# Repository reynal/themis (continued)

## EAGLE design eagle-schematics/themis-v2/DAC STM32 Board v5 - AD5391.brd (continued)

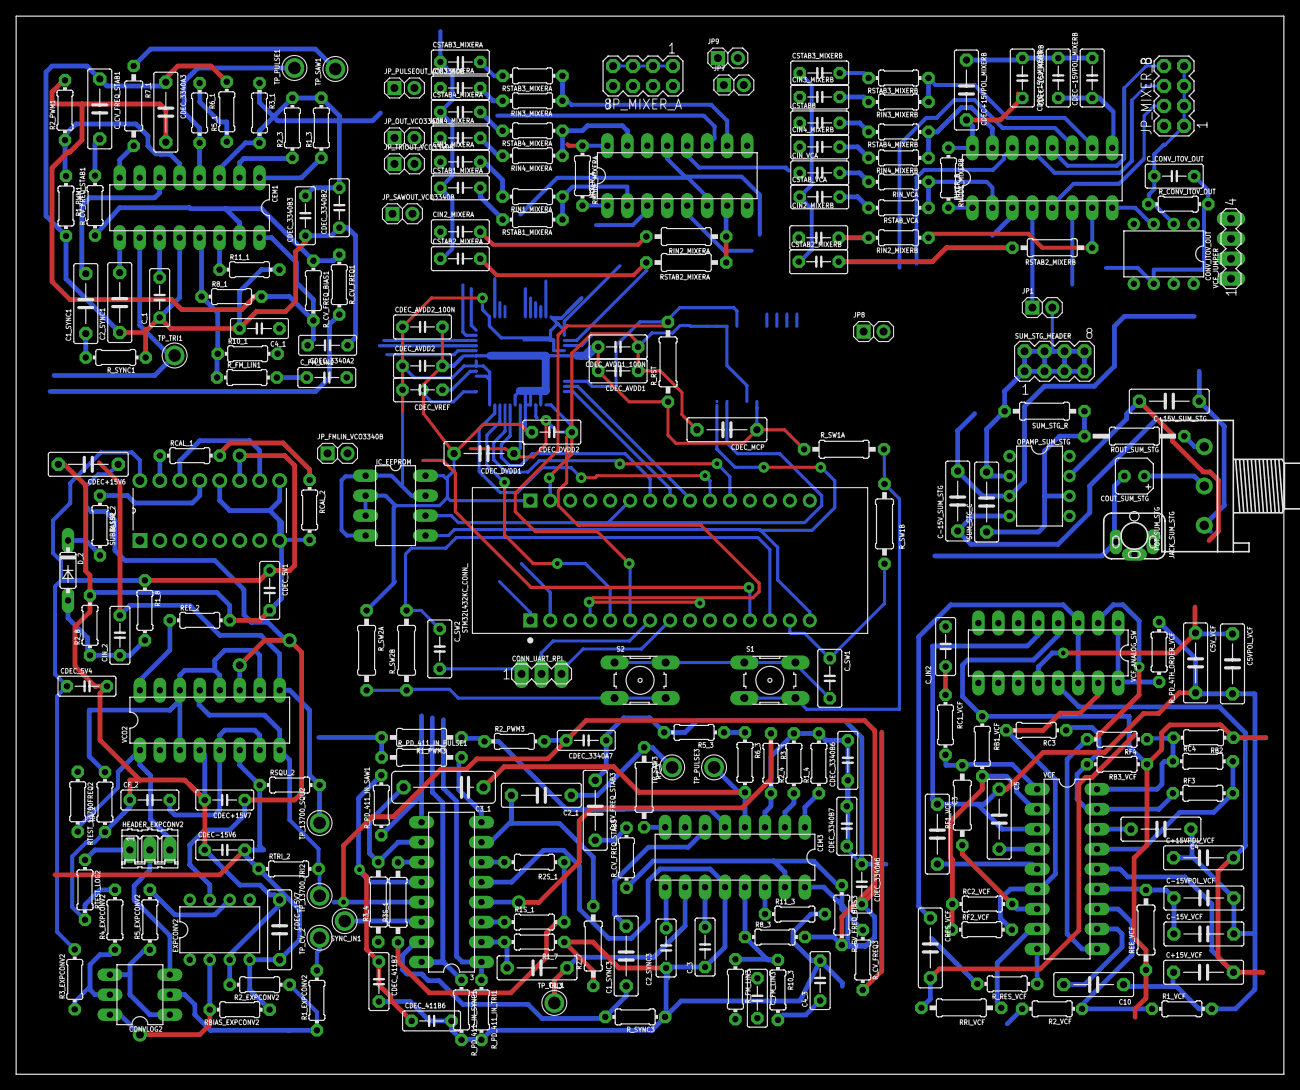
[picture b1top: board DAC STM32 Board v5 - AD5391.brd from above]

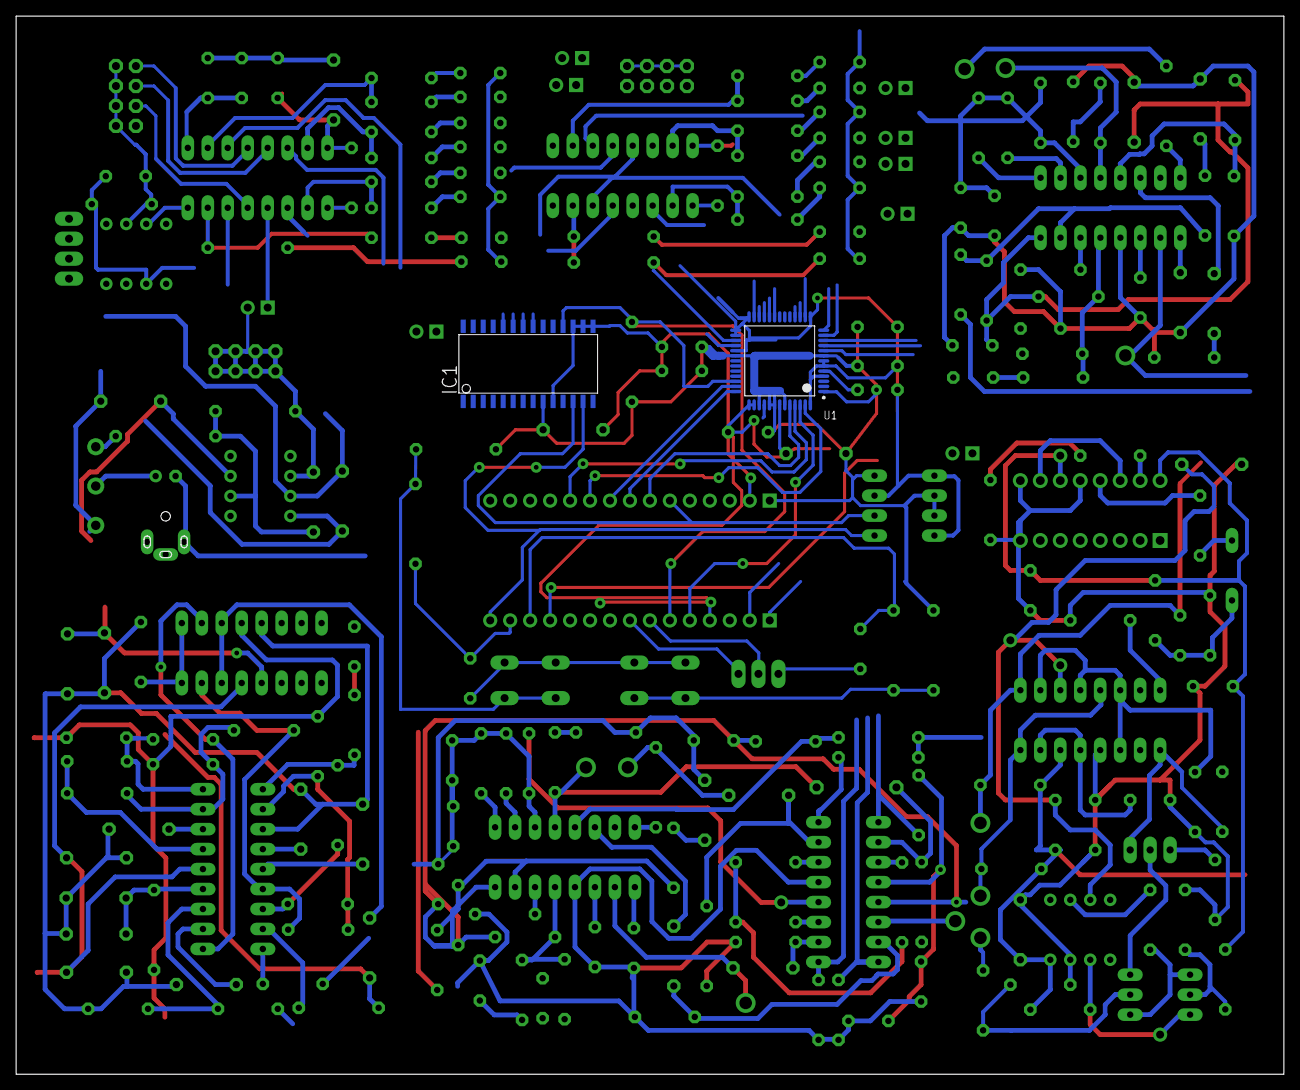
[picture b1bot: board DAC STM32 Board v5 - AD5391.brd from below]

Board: 2 copper layers, 161.3 x 134.6 mm, 229 parts (2 on the bottom side), 173 nets.

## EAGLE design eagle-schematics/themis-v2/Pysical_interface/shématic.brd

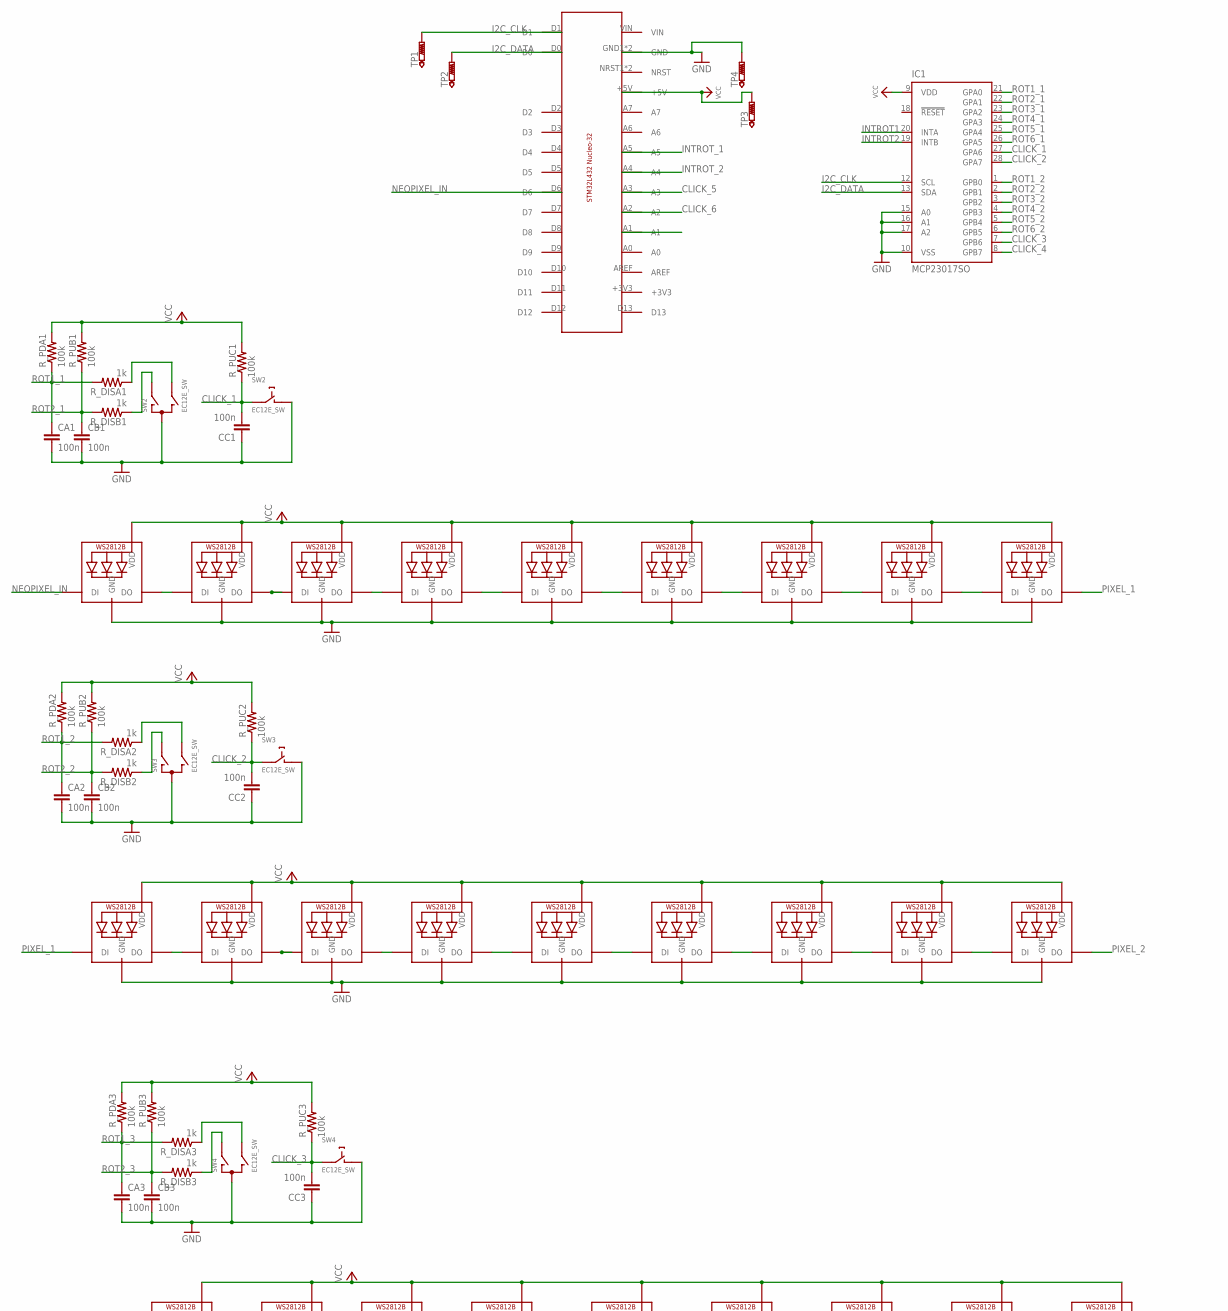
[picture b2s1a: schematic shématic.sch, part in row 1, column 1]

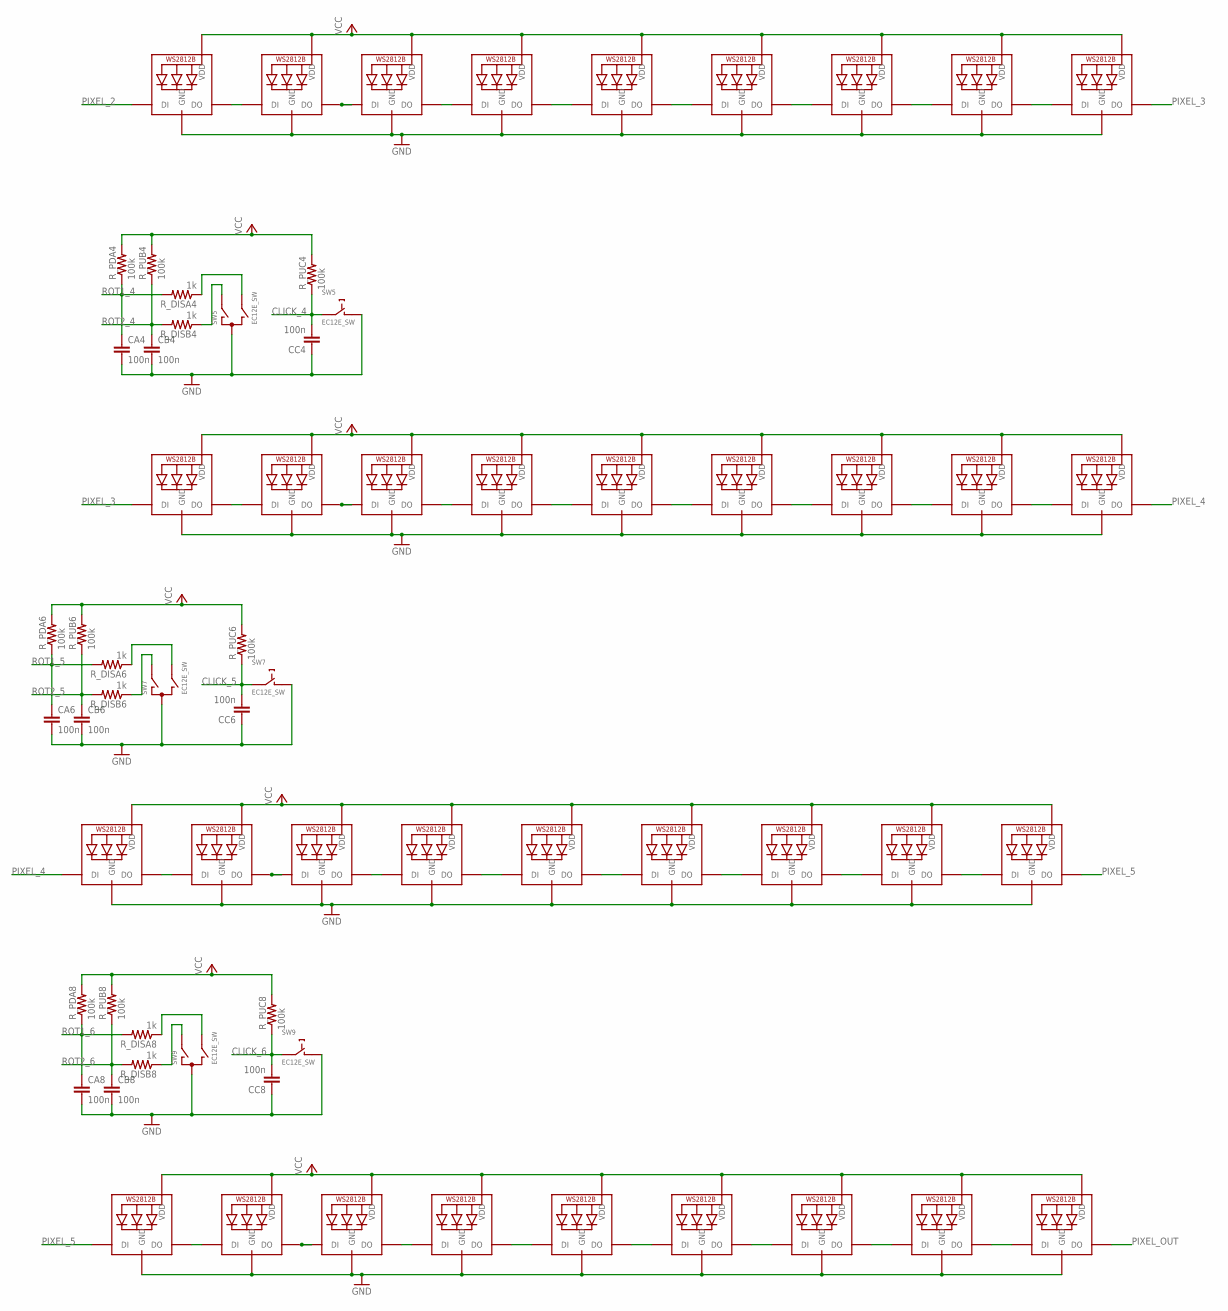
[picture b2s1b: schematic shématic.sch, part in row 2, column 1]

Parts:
CA1, CA2, CA3, CA4, CA6, CA8: 100n; C1210
CB1, CB2, CB3, CB4, CB6, CB8: 100n; C1210
CC1, CC2, CC3, CC4, CC6, CC8: 100n; C1210
IC1: MCP23017SO; SO28W
LED10, LED11, LED12, LED13, LED14, LED15, LED16, LED17, LED18, LED19, LED20, LED21, LED22, LED23, LED24, LED25, LED26, LED27, LED28, LED29, LED30, LED31, LED32, LED33, LED34, LED35, LED36, LED37, LED38, LED39, LED40, LED41, LED42, LED43, LED44, LED45, LED55, LED56, LED57, LED58, LED59, LED60, LED61, LED62, LED63, LED73, LED74, LED75, LED76, LED77, LED78, LED79, LED80, LED81: WS2812B5050; WS2812B
R_DISA1, R_DISA2, R_DISA3, R_DISA4, R_DISA6, R_DISA8: 1k; R1210
R_DISB1, R_DISB2, R_DISB3, R_DISB4, R_DISB6, R_DISB8: 1k; R1210
R_PDA1, R_PDA2, R_PDA3, R_PDA4, R_PDA6, R_PDA8: 100k; R1210
R_PUB1, R_PUB2, R_PUB3, R_PUB4, R_PUB6, R_PUB8: 100k; R1210
R_PUC1, R_PUC2, R_PUC3, R_PUC4, R_PUC6, R_PUC8: 100k; R1210
SW2, SW3, SW4, SW5, SW7, SW9: EC12E_SW; ALPS_EC12E_SW
TP1, TP2, TP3, TP4: PTR1PAD1-13Y; P1-13Y
U$2: NUCLEO-HEADER

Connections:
CLICK_1: CC1.2, IC1.27 (GPA6), R_PUC1.1, SW2.E (2)
CLICK_2: CC2.2, IC1.28 (GPA7), R_PUC2.1, SW3.E (2)
CLICK_3: CC3.2, IC1.7 (GPB6), R_PUC3.1, SW4.E (2)
CLICK_4: CC4.2, IC1.8 (GPB7), R_PUC4.1, SW5.E (2)
CLICK_5: CC6.2, R_PUC6.1, SW7.E (2), U$2.A3
CLICK_6: CC8.2, R_PUC8.1, SW9.E (2), U$2.A2
GND: CA1.2, CA2.2, CA3.2, CA4.2, CA6.2, CA8.2, CB1.2, CB2.2, CB3.2, CB4.2, CB6.2, CB8.2, CC1.1, CC2.1, CC3.1, CC4.1, CC6.1, CC8.1, IC1.10 (VSS), IC1.15 (A0), IC1.16 (A1), IC1.17 (A2), LED10.3-GND (GND), LED11.3-GND (GND), LED12.3-GND (GND), LED13.3-GND (GND), LED14.3-GND (GND), LED15.3-GND (GND), LED16.3-GND (GND), LED17.3-GND (GND), LED18.3-GND (GND), LED19.3-GND (GND), LED20.3-GND (GND), LED21.3-GND (GND), LED22.3-GND (GND), LED23.3-GND (GND), LED24.3-GND (GND), LED25.3-GND (GND), LED26.3-GND (GND), LED27.3-GND (GND), LED28.3-GND (GND), LED29.3-GND (GND), LED30.3-GND (GND), LED31.3-GND (GND), LED32.3-GND (GND), LED33.3-GND (GND), LED34.3-GND (GND), LED35.3-GND (GND), LED36.3-GND (GND), LED37.3-GND (GND), LED38.3-GND (GND), LED39.3-GND (GND), LED40.3-GND (GND), LED41.3-GND (GND), LED42.3-GND (GND), LED43.3-GND (GND), LED44.3-GND (GND), LED45.3-GND (GND), LED55.3-GND (GND), LED56.3-GND (GND), LED57.3-GND (GND), LED58.3-GND (GND), LED59.3-GND (GND), LED60.3-GND (GND), LED61.3-GND (GND), LED62.3-GND (GND), LED63.3-GND (GND), LED73.3-GND (GND), LED74.3-GND (GND), LED75.3-GND (GND), LED76.3-GND (GND), LED77.3-GND (GND), LED78.3-GND (GND), LED79.3-GND (GND), LED80.3-GND (GND), LED81.3-GND (GND), SW2.C, SW2.D (1), SW3.C, SW3.D (1), SW4.C, SW4.D (1), SW5.C, SW5.D (1), SW7.C, SW7.D (1), SW9.C, SW9.D (1), TP4.TP, U$2.GND1 (GND), U$2.GND2 (GND)
I2C_CLK: IC1.12 (SCL), TP1.TP, U$2.D1
I2C_DATA: IC1.13 (SDA), TP2.TP, U$2.D0
INTROT1: IC1.20 (INTA)
INTROT2: IC1.19 (INTB)
INTROT_1: U$2.A5
INTROT_2: U$2.A4
unnamed: LED10.2-DOUT (DO), LED11.4-DIN (DI)
unnamed: LED11.2-DOUT (DO), LED12.4-DIN (DI)
unnamed: LED12.2-DOUT (DO), LED13.4-DIN (DI)
unnamed: LED13.2-DOUT (DO), LED14.4-DIN (DI)
unnamed: R_DISB1.1, SW2.A
unnamed: R_DISA1.1, SW2.B
unnamed: LED17.2-DOUT (DO), LED18.4-DIN (DI)
unnamed: LED16.2-DOUT (DO), LED17.4-DIN (DI)
unnamed: LED15.2-DOUT (DO), LED16.4-DIN (DI)
unnamed: LED14.2-DOUT (DO), LED15.4-DIN (DI)
unnamed: LED19.2-DOUT (DO), LED20.4-DIN (DI)
unnamed: LED20.2-DOUT (DO), LED21.4-DIN (DI)
unnamed: LED21.2-DOUT (DO), LED22.4-DIN (DI)
unnamed: LED22.2-DOUT (DO), LED23.4-DIN (DI)
unnamed: R_DISB2.1, SW3.A
unnamed: R_DISA2.1, SW3.B
unnamed: LED26.2-DOUT (DO), LED27.4-DIN (DI)
unnamed: LED25.2-DOUT (DO), LED26.4-DIN (DI)
unnamed: LED24.2-DOUT (DO), LED25.4-DIN (DI)
unnamed: LED23.2-DOUT (DO), LED24.4-DIN (DI)
unnamed: LED28.2-DOUT (DO), LED29.4-DIN (DI)
unnamed: LED29.2-DOUT (DO), LED30.4-DIN (DI)
unnamed: LED30.2-DOUT (DO), LED31.4-DIN (DI)
unnamed: LED31.2-DOUT (DO), LED32.4-DIN (DI)
unnamed: R_DISB3.1, SW4.A
unnamed: R_DISA3.1, SW4.B
unnamed: LED35.2-DOUT (DO), LED36.4-DIN (DI)
unnamed: LED34.2-DOUT (DO), LED35.4-DIN (DI)
unnamed: LED33.2-DOUT (DO), LED34.4-DIN (DI)
unnamed: LED32.2-DOUT (DO), LED33.4-DIN (DI)
unnamed: LED37.2-DOUT (DO), LED38.4-DIN (DI)
unnamed: LED38.2-DOUT (DO), LED39.4-DIN (DI)
unnamed: LED39.2-DOUT (DO), LED40.4-DIN (DI)
unnamed: LED40.2-DOUT (DO), LED41.4-DIN (DI)
unnamed: R_DISB4.1, SW5.A
unnamed: R_DISA4.1, SW5.B
unnamed: LED44.2-DOUT (DO), LED45.4-DIN (DI)
unnamed: LED43.2-DOUT (DO), LED44.4-DIN (DI)
unnamed: LED42.2-DOUT (DO), LED43.4-DIN (DI)
unnamed: LED41.2-DOUT (DO), LED42.4-DIN (DI)
unnamed: LED55.2-DOUT (DO), LED56.4-DIN (DI)
unnamed: LED56.2-DOUT (DO), LED57.4-DIN (DI)
unnamed: LED57.2-DOUT (DO), LED58.4-DIN (DI)
unnamed: LED58.2-DOUT (DO), LED59.4-DIN (DI)
unnamed: R_DISB6.1, SW7.A
unnamed: R_DISA6.1, SW7.B
unnamed: LED62.2-DOUT (DO), LED63.4-DIN (DI)
unnamed: LED61.2-DOUT (DO), LED62.4-DIN (DI)
unnamed: LED60.2-DOUT (DO), LED61.4-DIN (DI)
unnamed: LED59.2-DOUT (DO), LED60.4-DIN (DI)
unnamed: LED73.2-DOUT (DO), LED74.4-DIN (DI)
unnamed: LED74.2-DOUT (DO), LED75.4-DIN (DI)
unnamed: LED75.2-DOUT (DO), LED76.4-DIN (DI)
unnamed: LED76.2-DOUT (DO), LED77.4-DIN (DI)
unnamed: R_DISB8.1, SW9.A
unnamed: R_DISA8.1, SW9.B
unnamed: LED80.2-DOUT (DO), LED81.4-DIN (DI)
unnamed: LED79.2-DOUT (DO), LED80.4-DIN (DI)
unnamed: LED78.2-DOUT (DO), LED79.4-DIN (DI)
unnamed: LED77.2-DOUT (DO), LED78.4-DIN (DI)
NEOPIXEL_IN: LED10.4-DIN (DI), U$2.D6
PIXEL_1: LED18.2-DOUT (DO), LED19.4-DIN (DI)
PIXEL_2: LED27.2-DOUT (DO), LED28.4-DIN (DI)
PIXEL_3: LED36.2-DOUT (DO), LED37.4-DIN (DI)
PIXEL_4: LED45.2-DOUT (DO), LED55.4-DIN (DI)
PIXEL_5: LED63.2-DOUT (DO), LED73.4-DIN (DI)
PIXEL_OUT: LED81.2-DOUT (DO)
ROT1_1: CA1.1, IC1.21 (GPA0), R_DISA1.2, R_PDA1.1
ROT1_2: CA2.1, IC1.1 (GPB0), R_DISA2.2, R_PDA2.1
ROT1_3: CA3.1, R_DISA3.2, R_PDA3.1
ROT1_4: CA4.1, R_DISA4.2, R_PDA4.1
ROT1_5: CA6.1, R_DISA6.2, R_PDA6.1
ROT1_6: CA8.1, R_DISA8.2, R_PDA8.1
ROT2_1: CB1.1, IC1.22 (GPA1), R_DISB1.2, R_PUB1.1
ROT2_2: CB2.1, IC1.2 (GPB1), R_DISB2.2, R_PUB2.1
ROT2_3: CB3.1, R_DISB3.2, R_PUB3.1
ROT2_4: CB4.1, R_DISB4.2, R_PUB4.1
ROT2_5: CB6.1, R_DISB6.2, R_PUB6.1
ROT2_6: CB8.1, R_DISB8.2, R_PUB8.1
ROT3_1: IC1.23 (GPA2)
ROT3_2: IC1.3 (GPB2)
ROT4_1: IC1.24 (GPA3)
ROT4_2: IC1.4 (GPB3)
ROT5_1: IC1.25 (GPA4)
ROT5_2: IC1.5 (GPB4)
ROT6_1: IC1.26 (GPA5)
ROT6_2: IC1.6 (GPB5)
VCC: IC1.9 (VDD), LED10.1-VDD (VDD), LED11.1-VDD (VDD), LED12.1-VDD (VDD), LED13.1-VDD (VDD), LED14.1-VDD (VDD), LED15.1-VDD (VDD), LED16.1-VDD (VDD), LED17.1-VDD (VDD), LED18.1-VDD (VDD), LED19.1-VDD (VDD), LED20.1-VDD (VDD), LED21.1-VDD (VDD), LED22.1-VDD (VDD), LED23.1-VDD (VDD), LED24.1-VDD (VDD), LED25.1-VDD (VDD), LED26.1-VDD (VDD), LED27.1-VDD (VDD), LED28.1-VDD (VDD), LED29.1-VDD (VDD), LED30.1-VDD (VDD), LED31.1-VDD (VDD), LED32.1-VDD (VDD), LED33.1-VDD (VDD), LED34.1-VDD (VDD), LED35.1-VDD (VDD), LED36.1-VDD (VDD), LED37.1-VDD (VDD), LED38.1-VDD (VDD), LED39.1-VDD (VDD), LED40.1-VDD (VDD), LED41.1-VDD (VDD), LED42.1-VDD (VDD), LED43.1-VDD (VDD), LED44.1-VDD (VDD), LED45.1-VDD (VDD), LED55.1-VDD (VDD), LED56.1-VDD (VDD), LED57.1-VDD (VDD), LED58.1-VDD (VDD), LED59.1-VDD (VDD), LED60.1-VDD (VDD), LED61.1-VDD (VDD), LED62.1-VDD (VDD), LED63.1-VDD (VDD), LED73.1-VDD (VDD), LED74.1-VDD (VDD), LED75.1-VDD (VDD), LED76.1-VDD (VDD), LED77.1-VDD (VDD), LED78.1-VDD (VDD), LED79.1-VDD (VDD), LED80.1-VDD (VDD), LED81.1-VDD (VDD), R_PDA1.2, R_PDA2.2, R_PDA3.2, R_PDA4.2, R_PDA6.2, R_PDA8.2, R_PUB1.2, R_PUB2.2, R_PUB3.2, R_PUB4.2, R_PUB6.2, R_PUB8.2, R_PUC1.2, R_PUC2.2, R_PUC3.2, R_PUC4.2, R_PUC6.2, R_PUC8.2, TP3.TP, U$2.+5V

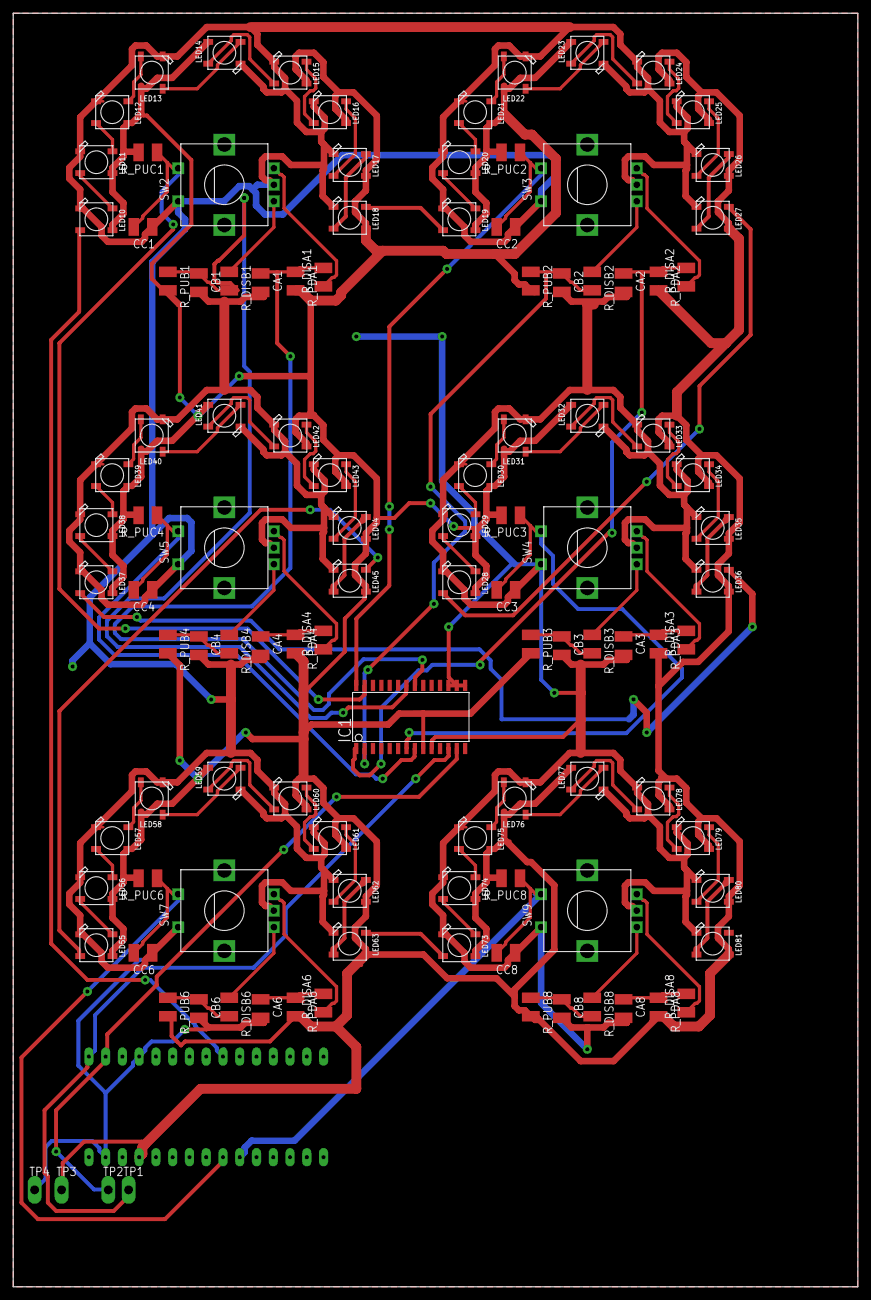
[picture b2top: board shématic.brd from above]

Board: 2 copper layers, 128.0 x 193.0 mm, 114 parts (1 on the bottom side), 88 nets.

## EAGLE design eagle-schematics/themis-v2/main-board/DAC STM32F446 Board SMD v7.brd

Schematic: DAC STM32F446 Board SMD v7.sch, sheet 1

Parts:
0V/5V/-15V/+15V: MA04-2
3V3: LED-0805; 0805-LED
5V: LED-0603; 0603-LED
24C04: 24C04AP; DIL8
2164A, 2164B: SSM2164; DIL16
3340A, 3340B: CEM3340; DIL16
+15V: LED-0805; 0805-LED
-15V: LED-0805; 0805-LED
A1, A2, A3, A4: T; TESTPOINT_63
A02/1/12/11: MA04-1
A010/9/8/7/3/4/5/6: MA08-1
ABCD: MA04-1
AD5644: ANALOG_DEVICES_AD5644RBRMZ-5ANALOG_DEVICES_AD5644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; ANALOG_DEVICES_AD5644RBRMZ-5_0
ADG453: ADG453BRZ; SOIC127P600X175-16N
ANAIN: MA02-1
B1, B2, B3, B4: T; TESTPOINT_63
BH2221: BH2221FV; SOP65P780X200-20N
C1, C2, C5, C6, C9, C10, C11, C16, C33, C34, C39, C40, C51, C63, C64: 100n; C0805
C3, C4, C7, C8: 1n; C0805
C12, C13, C14, C15: 10n; C0805
C17, C18, C19, C20, C21, C22, C23, C24, C41: 470n; C0805
C25, C26, C27, C28, C29, C30, C31, C32: 560p; C0805
C35, C46: 100p; C0805
C36, C37, C38: 4.7u; C0805
C42, C44: 1u; C0805
C43, C45, C49, C52: 300p; C0805
C50: 22u; B45181A
C53, C54, C58, C59, C62, C73: 10u; CPOL2917
C55, C66, C67, C68, C69, C70: 0.1uF; C0805
C56, C57: 12pF; C0805
C60: 2.2uF; C0805
C61, C72: 100n; C1206
C65: 100 uF; CPOL2917
C71: 1.0uF; C0805
C74, C75, C76, C77, C78, C79, C80, C81, C82, C83, C84, C85, C86, C87, C88: 1u; C1206
CAL_A: SYNC_IN; TESTPOINT_63
CAL_B: CALIB B; TESTPOINT_63
CAL_IN_A: TESTPOINT; TESTPOINT_63
CAL_IN_B: TESTPOINT; TESTPOINT_63
CUTOFF: TESTPOINT; TESTPOINT_63
CV_A: CV; TESTPOINT_63
CV_B: CV; TESTPOINT_63
CV_TM: 100k; 6MM
EXT: MA04-1
F446: STM32F446RCT7; QFP50P1200X1200X160-64N
FM_B: FMLIN; TESTPOINT_63
GAINS: GAIN_CTRL; MA08-1
GREEN: LED-0805; 0805-LED
HIGH_A: 100k; 6MM
HIGH_B: 100k; 6MM
HOLE1, HOLE2, HOLE3, HOLE4: HOLES_MOUNT-PAD-ROUND-0.096-NS; HOLES_096-PAD-NS
I2C: MA03-1
IN9, IN10: TESTPOINT; TESTPOINT_63
IN34: IN34; MA02-1
ITOV: NE5534AN; DIL08
I_SUM: ITOV; MA08-2
JACK: 1502_01
L1: 1 uH; L0805
LOW_A: 100k; 6MM
LOW_B: 100k; 6MM
MIDI: MA03-1
MIXOUT: TESTPOINT; TESTPOINT_63
MODRING: LM13700M; SO16
Q: TESTPOINT; TESTPOINT_63
Q1: 16MHz; Q-HC-46X
Q_TM: 100k; 6MM
R1, R3: 330k; R0805
R2, R4: 68k; R0805
R5, R6, R51, R52, R63, R82, R83, R85, R86, R93, R94: 10k; R0805
R7, R8: 33k; R0805
R9, R10: 820; R0805
R11, R12: 24k; R0805
R13, R27: 470k; R0805
R14, R15, R16, R17: 5.6k; R0805
R18, R19: 1.8k; R0805
R20, R22, R23, R24, R32, R37, R38, R39, R40, R41, R42, R43, R73, R92: 470; R0805
R21: 1M; R0805
R25, R26: 1.5M; R0805
R28, R29, R30, R31, R33, R34, R35, R36, R46, R47, R58: 27k; R0805
R44, R45: 8.2k; R0805
R48: 33K; R0805
R49, R53, R62, R66, R67, R68, R72, R74, R78, R79: 100k; R0805
R50, R56, R84, R88, R90, R95: 1k; R0805
R54: 1.5k; R0805
R55: 51k; R0805
R57: 4.7k; R0805
R59, R64, R70, R76: 91k; R0805
R60, R69: 47k; R0805
R61: 22k; R0805
R65, R71, R77: 220k; R0805
R75: 100kB; 3RP/1610N
R80: 100; R0805
R81: 10K; R0805
R87: 1; R0805
R89, R91: 180; R0805
RED1, RED2: LED-0603; 0603-LED
RST: 10-XX; B3F-10XX
SAW_A: S; TESTPOINT_63
SAW_B: S; TESTPOINT_63
SD3: SD3; MA02-1
SD4: SD4; MA02-1
SQU_A: P; TESTPOINT_63
SQU_B: P; TESTPOINT_63
STLINK: 75867-331LF; MA03-2
SUB: 4027D; SO16
SUB2, SUB4: T; TESTPOINT_63
SUB_IN: T; TESTPOINT_63
SUM_CON: MA04-2
SUM_OPAMP: NE5534AN; DIL08
SW1, SW2: 10-XX; B3F-10XX
SYNC_A: SYNC_IN; TESTPOINT_63
SYNC_B: SYNC_IN; TESTPOINT_63
TEMCOA: 10k; 6MM
TEMCOB: 10k; 6MM
TLV75533: TLV75533PDBVR; SOT95P280X145-5N
TRI_A: T; TESTPOINT_63
TRI_B: T; TESTPOINT_63
VCA: LM13700M; SO16
VCA_CV: TESTPOINT; TESTPOINT_63
VCA_IN: TESTPOINT; TESTPOINT_63
VCA_OUT: TESTPOINT; TESTPOINT_63
VCF1: AS3320; DIL18
VCF_IN: TESTPOINT; TESTPOINT_63
VCF_OUT: TESTPOINT; TESTPOINT_63
XIN: TESTPOINT; TESTPOINT_63
XMOD: TESTPOINT; TESTPOINT_63

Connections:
3V3: 24C04.2 (A1), 24C04.3 (A2), 24C04.8 (VCC), C65.+, C66.2, C67.2, C68.2, C69.2, C70.2, C71.2, F446.1 (VBAT), F446.13 (VDDA/VREF+), F446.19 (VDD_4), F446.32 (VDD_1), F446.48 (VDD_2), F446.64 (VDD_3), L1.2, R79.1, R82.1, R83.1, R84.2, R88.2, R95.1, STLINK.1
5V: 0V/5V/-15V/+15V.3, 0V/5V/-15V/+15V.4, AD5644.9 (VDD), ADG453.12 (VL), BH2221.10 (VDD), BH2221.11 (VCC), C51.1, C58.+, C59.+, C61.2, C62.+, C72.2, C73.+, C76.2, R92.1, TLV75533.1 (IN), TLV75533.3 (EN)
2164_IN1_MIXA: 2164A.2 (I_IN1), R33.1, R40.1
2164_IN2_MIXA: 2164A.7 (I_IN2), R34.1, R41.1
2164_IN2_MIXB: 2164B.7 (I_IN2), R29.1, R37.1
2164_IN3_MIXA: 2164A.10 (I_IN3), R35.1, R42.1
2164_IN3_MIXB: 2164B.10 (I_IN3), R30.1, R38.1
2164_IN4_MIXA: 2164A.15 (I_IN4), R36.1, R43.1
2164_IN4_MIXB: 2164B.15 (I_IN4), R31.1, R39.1
2164_IN4_MIXB1: 2164B.2 (I_IN1), R28.1, R32.1
2164_MODE_MIXB: 2164B.1 (MODE), R44.2
2164_OUT2_MIXA: 2164A.5 (I_OUT2), I_SUM.4
2164_OUT2_MIXB: 2164B.5 (I_OUT2), I_SUM.14
2164_OUT3_MIXA: 2164A.12 (I_OUT3), I_SUM.8
2164_OUT3_MIXB: 2164B.12 (I_OUT3), I_SUM.16
2164_OUT4_MIXA: 2164A.13 (I_OUT4), I_SUM.6
2164_OUT4_MIXB: 2164B.13 (I_OUT4), I_SUM.12
+15V: 0V/5V/-15V/+15V.7, 0V/5V/-15V/+15V.8, 2164A.16 (V+), 2164B.16 (V+), 3340A.16 (VCC), 3340B.16 (VCC), ADG453.13 (VDD), C5.2, C6.2, C33.2, C39.2, C53.+, C74.2, C77.2, C78.2, C79.2, C80.2, C81.2, C82.2, C83.2, ITOV.7 (V+), LOW_A.E, LOW_B.E, MODRING.11 (V+), R1.2, R3.2, R25.2, R26.2, R44.1, R45.1, R51.1, R60.2, R94.1, SUM_OPAMP.7 (V+), VCA.11 (V+), VCF1.14 (V+)
-15V: 0V/5V/-15V/+15V.5, 0V/5V/-15V/+15V.6, 2164A.9 (V-), 2164B.9 (V-), ADG453.4 (VSS), C34.1, C54.-, C75.2, C84.2, C85.2, C86.2, C87.2, C88.2, ITOV.4 (V-), MODRING.6 (V-), R9.1, R10.1, R54.1, R63.1, R65.1, R71.1, R77.1, R93.1, SUM_OPAMP.4 (V-)
AD5644_CLK: AD5644.7 (SCLK), F446.29 (PB10)
AD5644_DI: AD5644.8 (DIN), F446.9 (PC1)
AD5644_SYNC: AD5644.6 (!SYNC!), F446.33 (PB12)
BH2221_CLK: BH2221.16 (CLK), F446.21 (PA5)
BH2221_DI: BH2221.17 (DI), F446.23 (PA7)
BH2221_LD: BH2221.15 (LD), F446.20 (PA4)
BIAS_VCA: C37.1, R50.2, R51.2, R52.1, SUM_OPAMP.3 (+IN), VCA.4 (IN_N)
BOOT1: F446.60 (BOOT0), R81.1
CALIB_3340A: CAL_A.P$1, R6.1, R8.1
CALIB_3340B: CAL_B.P$1, R5.1, R7.1
CALIB_IN_3340A: CAL_IN_A.P$1, F446.14 (PA0)
CALIB_IN_3340B: CAL_IN_B.P$1, F446.15 (PA1)
CAP1_VCF: C43.2, VCF1.5 (CAP)
CAP2_VCF: C45.2, VCF1.4 (CAP)
CAP3_VCF: C49.2, VCF1.16 (CAP)
CAP4_VCF: C52.2, VCF1.11 (CAP)
CV_CUTOFF: CUTOFF.P$1, CV_TM.E
CV_FREQ_3340A: CV_A.P$1, HIGH_A.E
CV_FREQ_3340B: CV_B.P$1, HIGH_B.E
CV_PWM_3340A: 3340A.5 (PWM_CTRL), R3.1, R4.1
CV_PWM_3340B: 3340B.5 (PWM_CTRL), R1.1, R2.1
CV_RES: Q.P$1, Q_TM.E, Q_TM.S
CV_VCA: R58.1, VCA_CV.P$1
EXT1: EXT.1, F446.50 (PA15)
EXT2: EXT.2, F446.51 (PC10)
EXT3: EXT.3, F446.52 (PC11)
EXT4: EXT.4, F446.53 (PC12)
FEEDBACK_VCF: ADG453.2 (D1), ADG453.15 (D2), C44.1
FMLIN_3340B: C11.2, FM_B.P$1
FREQ_CTRL_3340A: 3340A.15 (FREQ_CTRL), HIGH_A.A, HIGH_A.S, LOW_A.A, LOW_A.S, R24.1
FREQ_CTRL_3340B: 3340B.15 (FREQ_CTRL), HIGH_B.A, HIGH_B.S, LOW_B.A, LOW_B.S, R23.1
FREQ_CV_VCF: CV_TM.S, VCF1.12 (FREQ_CV)
GAIN1_A: 2164A.3 (GAIN_VCA1), GAINS.8
GAIN1_B: 2164B.3 (GAIN_VCA1), GAINS.4
GAIN2_A: 2164A.6 (GAIN_VCA2), GAINS.5
GAIN2_B: 2164B.6 (GAIN_VCA2), GAINS.1
GAIN3_A: 2164A.11 (GAIN_VCA3), GAINS.6
GAIN3_B: 2164B.11 (GAIN_VCA3), GAINS.2
GAIN4_A: 2164A.14 (GAIN_VCA4), GAINS.7
GAIN4_B: 2164B.14 (GAIN_VCA4), GAINS.3
GND: 0V/5V/-15V/+15V.1, 0V/5V/-15V/+15V.2, 3V3.C, 5V.C, 24C04.1 (A0), 24C04.4 (GND), 24C04.7 (WP), 2164A.8 (GND), 2164B.8 (GND), 3340A.12 (GND), 3340B.12 (GND), +15V.C, -15V.A, AD5644.3 (GND), ADG453.5 (GND), BH2221.20 (GND), C1.1, C2.1, C5.1, C6.1, C7.1, C8.1, C9.1, C10.1, C12.1, C13.1, C14.2, C15.2, C16.2, C25.1, C26.1, C27.1, C28.1, C29.1, C30.1, C31.1, C32.1, C33.1, C34.2, C37.2, C39.1, C40.2, C43.1, C45.1, C49.1, C51.2, C52.1, C53.-, C54.+, C55.1, C56.1, C57.1, C58.-, C59.-, C60.1, C61.1, C62.-, C63.2, C64.2, C65.-, C66.1, C67.1, C68.1, C69.1, C70.1, C71.1, C72.1, C73.-, C74.1, C75.1, C76.1, C77.1, C78.1, C79.1, C80.1, C81.1, C82.1, C83.1, C84.1, C85.1, C86.1, C87.1, C88.1, CV_TM.A, F446.12 (VSSA/VREF-), F446.18 (VSS_4), F446.31 (VSS_1), F446.47 (VSS_2), F446.63 (VSS_3), GREEN.C, I2C.3, ITOV.3 (+IN), JACK.1, MIDI.3, MODRING.13 (IN_N), R2.2, R4.2, R5.2, R6.2, R13.1, R18.2, R19.2, R27.1, R52.2, R56.2, R61.1, R66.1, R68.1, R72.2, R75.1 (A), R81.2, RED1.C, RED2.C, RST.3, RST.4 (P1), STLINK.5, SUB.4 (R), SUB.7 (S), SUB.9 (S), SUB.12 (R), SW1.1 (S), SW1.2 (S1), SW2.1 (S), SW2.2 (S1), TLV75533.2 (GND), VCA.6 (V-), VCF1.3 (GND)
HEADIN_OPAMP_OUT: C46.2, R69.2, SUM_CON.1, SUM_CON.2, SUM_CON.3, SUM_CON.4, SUM_CON.5, SUM_CON.6, SUM_CON.7, SUM_CON.8, SUM_OPAMP.2 (-IN)
IN1_MIXERA: A1.P$1, C18.1
IN1_VCF: R59.2, R62.2, VCF1.1 (IN)
IN2_MIXERA: A2.P$1, C20.1
IN2_MIXERB: B2.P$1, C17.1
IN2_VCF: R64.1, R65.2, R67.1, VCF1.2 (IN)
IN3_MIXERA: A3.P$1, C23.1
IN3_MIXERB: B3.P$1, C21.1
IN3_VCF: R70.1, R71.2, R74.1, VCF1.17 (IN)
IN4_MIXERB: B4.P$1, C22.1
IN4_MIXERB1: B1.P$1, C19.1
IN4_VCF: R76.1, R77.2, R78.1, VCF1.18 (IN)
IN_VCF: C41.2, VCF_IN.P$1
IN_VCFORDER: ADG453.1 (IN1), ADG453.16 (IN2), R68.2
IOUT_VCA: VCA.5 (OUT), VCA_OUT.P$1
ITOV_IN: C35.1, ITOV.2 (-IN), I_SUM.1, I_SUM.3, I_SUM.5, I_SUM.7, I_SUM.9, I_SUM.11, I_SUM.13, I_SUM.15, R46.1, R47.1, R48.1
LED1_PWM: F446.22 (PA6), R90.1
LED2_PWM: F446.38 (PC7), R89.1
LED3_PWM: F446.26 (PB0), R91.1
LINEAR_CTRL_3340A: 3340A.13 (LINEAR_CTRL), R22.1, R26.1
LINEAR_CTRL_3340B: 3340B.13 (LINEAR_CTRL), R20.1, R21.1, R25.1
unnamed: 2164B.4 (I_OUT1), I_SUM.10
unnamed: 3340B.6 (HARD_SYNC), C3.2
unnamed: SUB.10 (J), SUB.14 (!Q)
unnamed: 2164A.4 (I_OUT1), I_SUM.2
unnamed: R82.2, R85.1, SW2.3, SW2.4 (P1)
unnamed: A4.P$1, C24.1
unnamed: R83.2, R86.1, SW1.3, SW1.4 (P1)
unnamed: C3.1, R13.2, SYNC_B.P$1
unnamed: ADG453.6 (S4), SD4.2
unnamed: C25.2, R32.2
unnamed: C19.2, R28.2
unnamed: MODRING.14 (IN_P), R53.2, R56.1
unnamed: C36.2, R49.2
unnamed: IN9.P$1, R46.2
unnamed: IN10.P$1, R47.2
unnamed: ADG453.7 (D4), SD4.1
unnamed: R58.2, VCA.1 (I_BIAS)
unnamed: ADG453.11 (S3), SD3.1
unnamed: A010/9/8/7/3/4/5/6.5, BH2221.2 (AO3)
unnamed: C26.2, R37.2
unnamed: A010/9/8/7/3/4/5/6.6, BH2221.3 (AO4)
unnamed: C27.2, R38.2
unnamed: A010/9/8/7/3/4/5/6.7, BH2221.4 (AO5)
unnamed: C28.2, R39.2
unnamed: A010/9/8/7/3/4/5/6.8, BH2221.5 (AO6)
unnamed: A010/9/8/7/3/4/5/6.4, BH2221.6 (AO7)
unnamed: A010/9/8/7/3/4/5/6.3, BH2221.7 (AO8)
unnamed: A010/9/8/7/3/4/5/6.2, BH2221.8 (AO9)
unnamed: A010/9/8/7/3/4/5/6.1, BH2221.9 (AO10)
unnamed: A02/1/12/11.1, BH2221.19 (AO2)
unnamed: A02/1/12/11.2, BH2221.18 (AO1)
unnamed: A02/1/12/11.3, BH2221.13 (AO12)
unnamed: A02/1/12/11.4, BH2221.12 (AO11)
unnamed: ABCD.1, AD5644.1 (VOUTA)
unnamed: ABCD.2, AD5644.2 (VOUTB)
unnamed: ADG453.10 (D3), SD3.2
unnamed: ADG453.9 (IN3), IN34.1, R72.1
unnamed: 2164A.1 (MODE), R45.2
unnamed: ABCD.3, AD5644.4 (VOUTC)
unnamed: ABCD.4, AD5644.5 (VOUTD)
unnamed: SUB.2 (!Q), SUB.6 (J)
unnamed: C16.1, SUB.5 (K), SUB.11 (K), SUB.16 (VDD)
unnamed: C38.1, R53.1
unnamed: MODRING.9 (E), R63.2
unnamed: C42.1, MODRING.16 (I_BIAS), R60.1
unnamed: C42.2, R57.1
unnamed: C36.1, R50.1, VCA.3 (IN_P)
unnamed: R89.2, RED1.A
unnamed: R57.2, XMOD.P$1
unnamed: C38.2, XIN.P$1
unnamed: MODRING.10 (B), MODRING.12 (OUT), R61.2
unnamed: R91.2, RED2.A
unnamed: 5V.A, R92.2
unnamed: -15V.C, R93.2
unnamed: +15V.A, R94.2
unnamed: GREEN.A, R90.2
unnamed: 3V3.A, R95.2
unnamed: ANAIN.2, F446.16 (PA2)
unnamed: ANAIN.1, F446.17 (PA3)
unnamed: C21.2, R30.2
unnamed: C17.2, R29.2
unnamed: C22.2, R31.2
unnamed: C30.2, R41.2
unnamed: C29.2, R40.2
unnamed: C31.2, R42.2
unnamed: C32.2, R43.2
unnamed: C18.2, R33.2
unnamed: C23.2, R35.2
unnamed: C20.2, R34.2
unnamed: C24.2, R36.2
unnamed: C56.2, Q1.1, R80.2
unnamed: R87.2, TLV75533.5 (OUT)
unnamed: L1.1, R87.1
unnamed: C41.1, R59.1
unnamed: C12.2, R23.2
unnamed: C14.1, R20.2
unnamed: 3340B.1 (MUL_GAIN1), TEMCOB.A
unnamed: R11.1, TEMCOB.E, TEMCOB.S
unnamed: C11.1, R21.2
unnamed: 3340B.8 (SAW_OUT), R14.2
unnamed: C13.2, R24.2
unnamed: C15.1, R22.2
unnamed: 3340A.1 (MUL_GAIN1), TEMCOA.A
unnamed: R12.1, TEMCOA.E, TEMCOA.S
unnamed: 3340A.8 (SAW_OUT), R15.2
unnamed: 3340A.6 (HARD_SYNC), C4.2
NRST: C55.2, F446.7 (NRST), R79.2, RST.1 (S), RST.2 (S1), STLINK.3
OSC_IN: F446.5 (PH0-OSC_IN), R80.1
OSC_OUT: C57.2, F446.6 (PH1-OSC_OUT), Q1.2
OUT1_VCF: R62.1, R64.2, VCF1.7 (OUT)
OUT2_VCF: ADG453.3 (S1), R67.2, R70.2, VCF1.6 (OUT)
OUT3_VCF: R74.2, R76.2, VCF1.15 (OUT)
OUT4_VCF: ADG453.14 (S2), R78.2, VCF1.10 (OUT)
OUT_JACK: C50.-, JACK.2 (3), JACK.3 (2)
OUT_MIXER: C35.2, ITOV.6 (OUT), MIXOUT.P$1, R48.2
OUT_OPAMP: C46.1, R69.1, R73.2, SUM_OPAMP.6 (OUT)
OUT_POT: C50.+, R73.1, R75.2 (S), R75.3 (E)
OUT_VCF: C44.2, R55.2, VCF_OUT.P$1
PULSE_3340A: 3340A.4 (PULSE_OUT), R8.2, SQU_A.P$1
PULSE_3340B: 3340B.4 (PULSE_OUT), R7.2, SQU_B.P$1
RES_CUR_IN_VCF: R55.1, VCF1.8 (IN_RES)
RES_CUR_VCF: Q_TM.A, VCF1.9 (RES_CUR)
SAW_3340A: R15.1, SAW_A.P$1
SAW_3340B: R14.1, SAW_B.P$1
SCALE_3340A: 3340A.14 (SCALE), R19.1
SCALE_3340B: 3340B.14 (SCALE), R18.1
SCL: 24C04.6 (SCL), F446.61 (PB8), I2C.2, R84.1
SDA: 24C04.5 (SDA), F446.62 (PB9), I2C.1, R88.1
SOFT_SYNC_3340A: 3340A.9 (SOFT_SYNC), C10.2
SOFT_SYNC_3340B: 3340B.9 (SOFT_SYNC), C9.2
SUB_IN: SUB.3 (CLK), SUB_IN.P$1
SUB_OUT2: SUB.1 (Q), SUB.13 (CLK), SUB2.P$1
SUB_OUT4: SUB.15 (Q), SUB4.P$1
SW1: C63.1, F446.40 (PC9), R85.2
SW2: C64.1, F446.39 (PC8), R86.2
SWCLK: F446.49 (PA14), STLINK.4
SWDIO: F446.46 (PA13), STLINK.2
SYNC_3340A: C4.1, R27.2, SYNC_A.P$1
TEMPCO2_VCOA: 3340A.2 (MUL_GAIN2), R17.1
TEMPCO2_VCOB: 3340B.2 (MUL_GAIN2), R16.1
TIMING_CAP_3340A: 3340A.11 (TIMING_CAP), C8.2
TIMING_CAP_3340B: 3340B.11 (TIMING_CAP), C7.2
TRI_3340A: 3340A.10 (TRI_OUT), TRI_A.P$1
TRI_3340B: 3340B.10 (TRI_OUT), TRI_B.P$1
USART1_RX: F446.59 (PB7), MIDI.1
USART1_TX: F446.58 (PB6), MIDI.2
VCAP1: C60.2, F446.30 (VCAP_1)
VCA_IN: R49.1, VCA_IN.P$1
VCF_ANASW_IN4: ADG453.8 (IN4), IN34.2, R66.2
VEE_VCF: C40.1, R54.2, VCF1.13 (V-)
VEE_VCOA: 3340A.3 (VEE), C2.2, R10.2, R12.2, R17.2
VEE_VCOB: 3340B.3 (VEE), C1.2, R9.2, R11.2, R16.2
VSS: SUB.8 (VSS)

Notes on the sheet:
Mixers A and B, 4 channels each (w/o VCA channel)
current -> voltage converter
According to the AS3320 datasheet, control voltage at pin 12 ranges from 0 to 200mV.
AS3320 VCF
Low Pass 2nd Order
Low Pass 4th Order
VCA
Connect 2 and 3 to bypass VCF. Otherwise connect 1 with 2, and 3 with 4.
STM32F446
Note: for a polyphonic synth, voice summing is performed here on the inverting input of the op amp.
Output summing stage
Protection againt short circuits
POWER
DAC (12 ch 8 bits + 4 ch 14 bits)
Connecté sur SPI1: - CLK=PA5 - MOSI=PA7 - NSS=PA4
Connecté sur SPI2: - CLK=PB10 - MOSI=PC1 - NSS=PB12
Channels: A01-12 = 8 bits B01-04 = 14 bits - A01 à A08 : 2164D vca - A09 : VCF cutoff - A10 : VCF Q - A11 : PWM 3340A - A12 : PWM 3340B - B01 : CV 3340A - B02 : CV 3340B - B03 : noise / wave generator (VCO #3) - B04 : VCA LM13700
VCO3340B (multiwave output)
VCO3340A (with wave selection switch)
MOD RING
!!!! Erreurs de routage à corriger !!!! Au moment de l'équipement de la carte : - inverser le condo polarisé C54 (+ côté 0V et non côté -15V) - inverser la LED "-15V" (pour la même raison)
